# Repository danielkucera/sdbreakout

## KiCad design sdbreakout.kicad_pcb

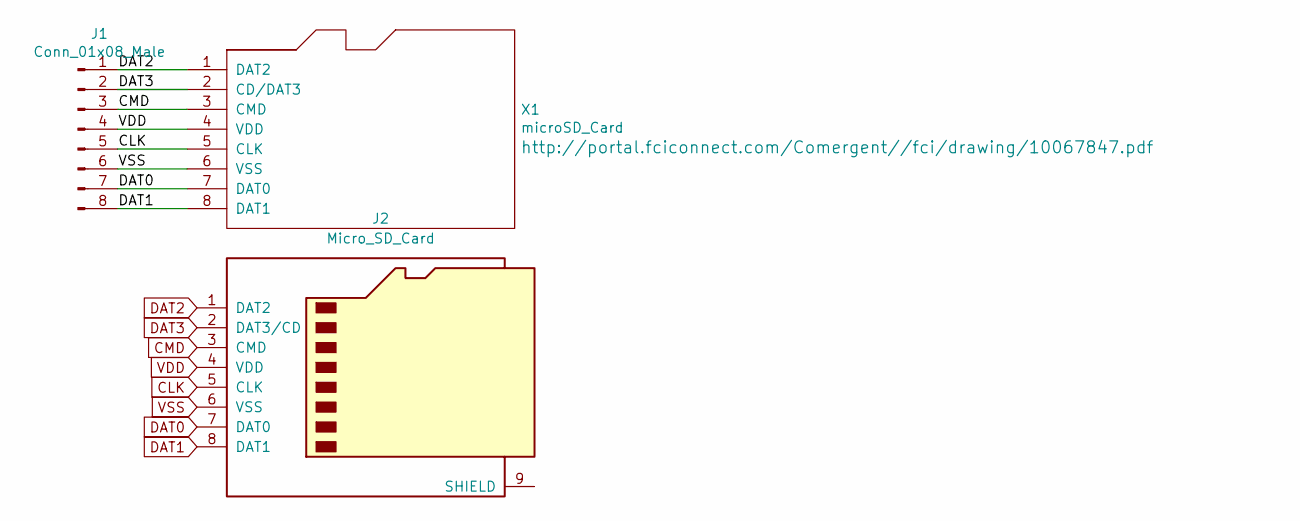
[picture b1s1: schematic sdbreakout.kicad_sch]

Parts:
J1: Conn_01x08_Male; PinHeader_2x04_P2.54mm_Vertical
J2: Micro_SD_Card
X1: microSD_Card

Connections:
CLK: J1.5, J2.5 (CLK), X1.5 (CLK)
CMD: J1.3, J2.3 (CMD), X1.3 (CMD)
DAT0: J1.7, J2.7 (DAT0), X1.7 (DAT0)
DAT1: J1.8, J2.8 (DAT1), X1.8 (DAT1)
DAT2: J1.1, J2.1 (DAT2), X1.1 (DAT2)
DAT3: J1.2, J2.2 (DAT3/CD), X1.2 (CD/DAT3)
VDD: J1.4, J2.4 (VDD), X1.4 (VDD)
VSS: J1.6, J2.6 (VSS), X1.6 (VSS)

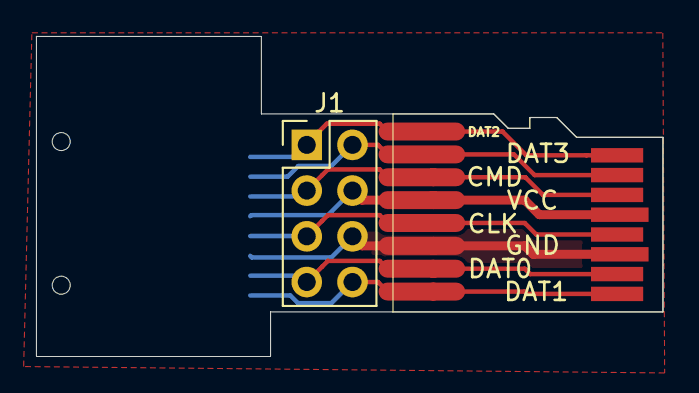
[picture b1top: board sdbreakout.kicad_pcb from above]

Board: 2 copper layers, 34.8 x 17.8 mm, 3 parts (1 on the bottom side), 8 nets.

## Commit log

2022-11-07 male plus female
2023-01-26 minor changes
